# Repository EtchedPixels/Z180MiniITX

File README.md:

# Z180 Mini-ITX Mother Board

This very much an initial work in progress.

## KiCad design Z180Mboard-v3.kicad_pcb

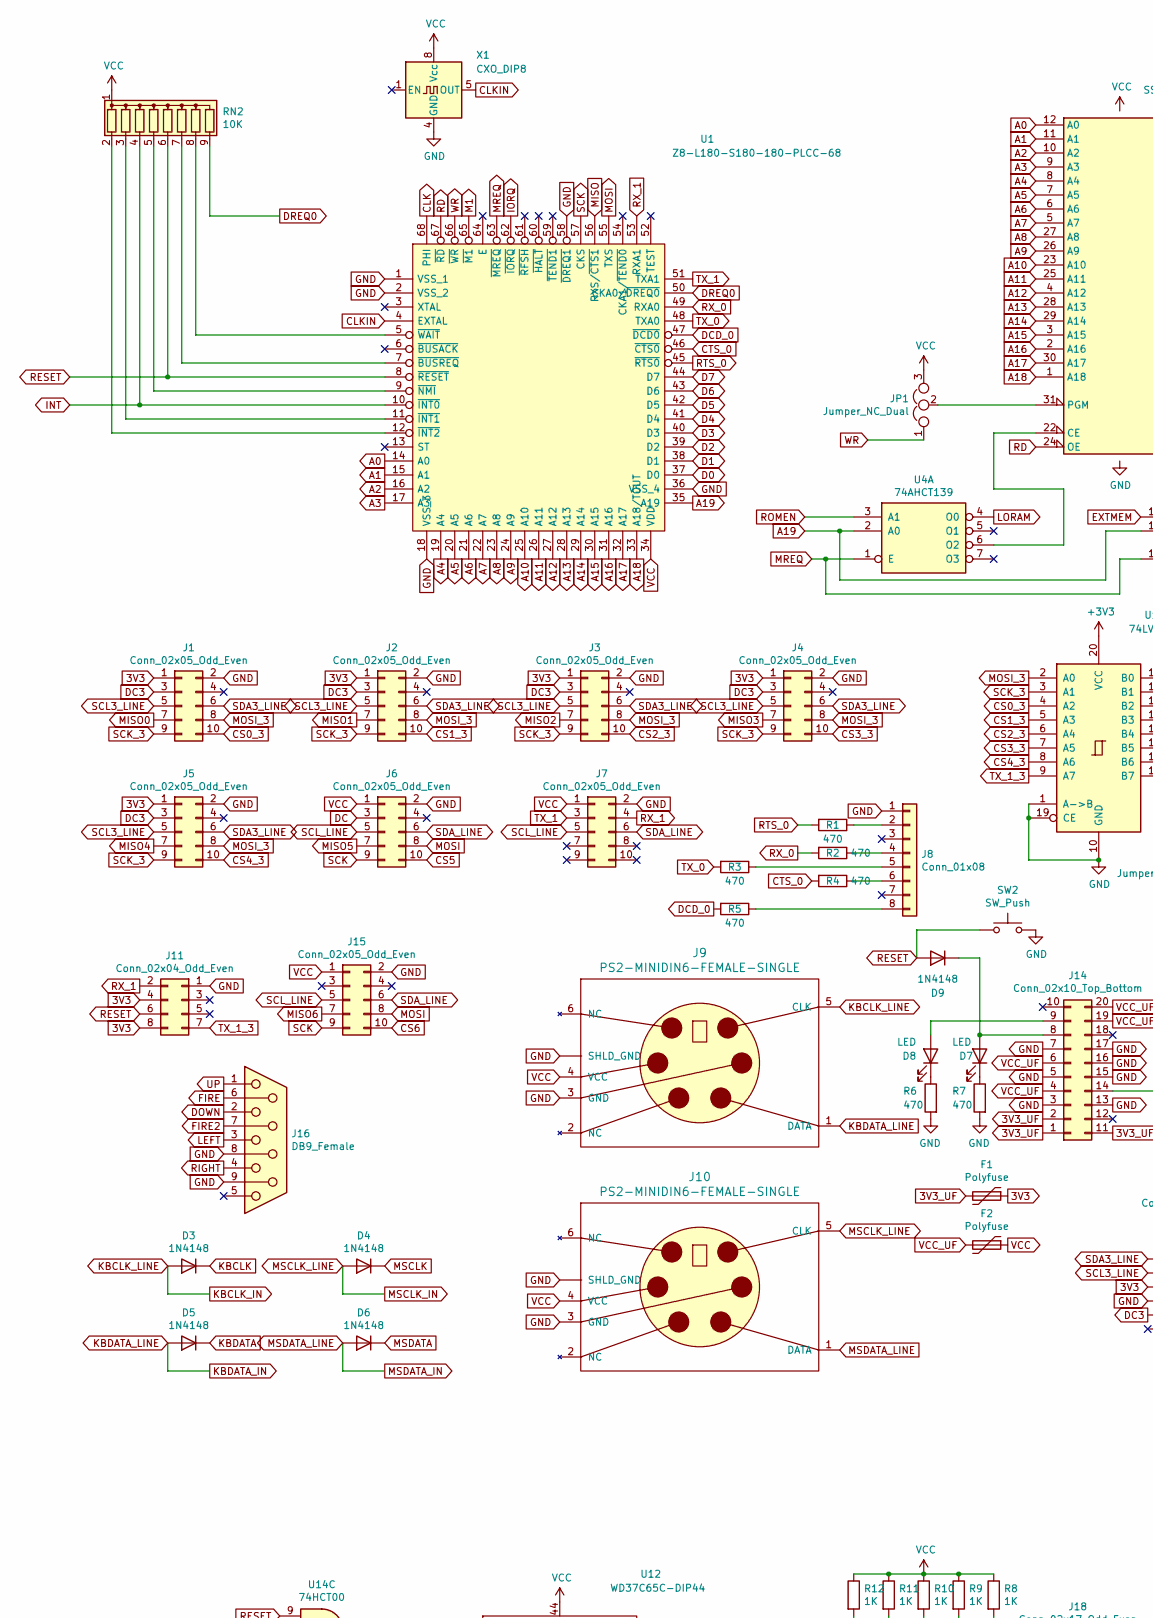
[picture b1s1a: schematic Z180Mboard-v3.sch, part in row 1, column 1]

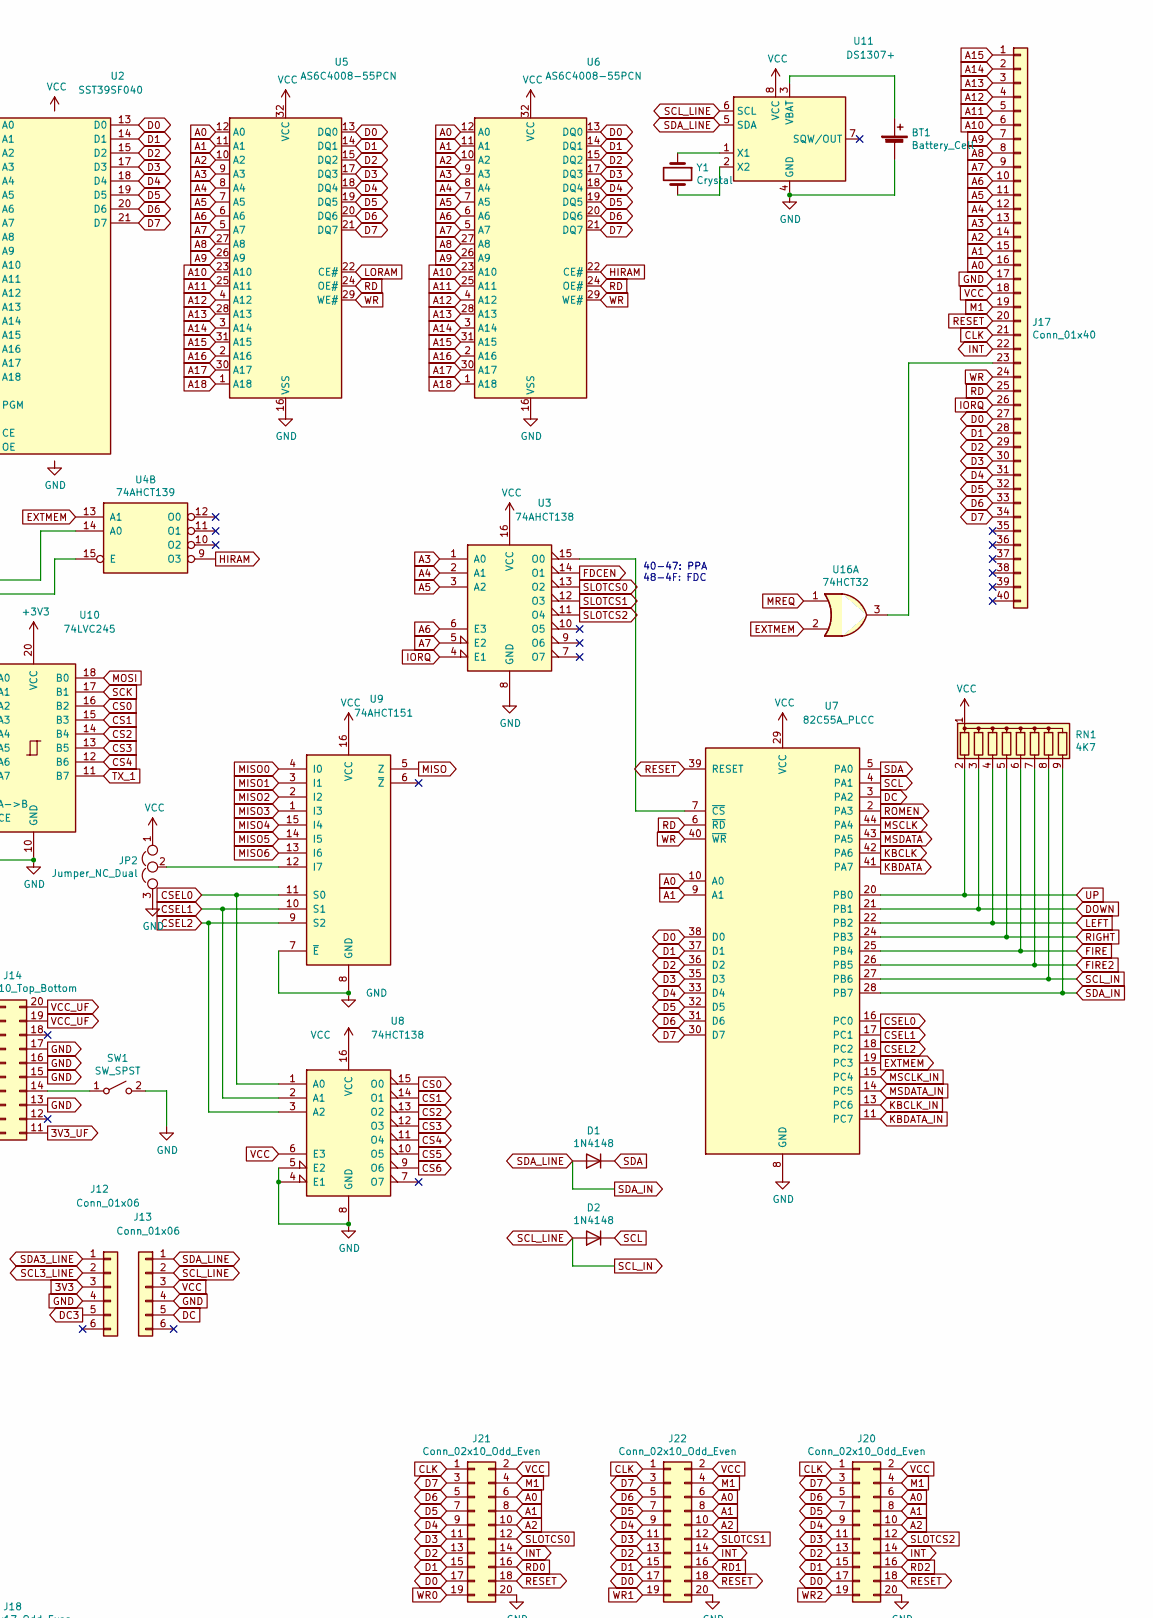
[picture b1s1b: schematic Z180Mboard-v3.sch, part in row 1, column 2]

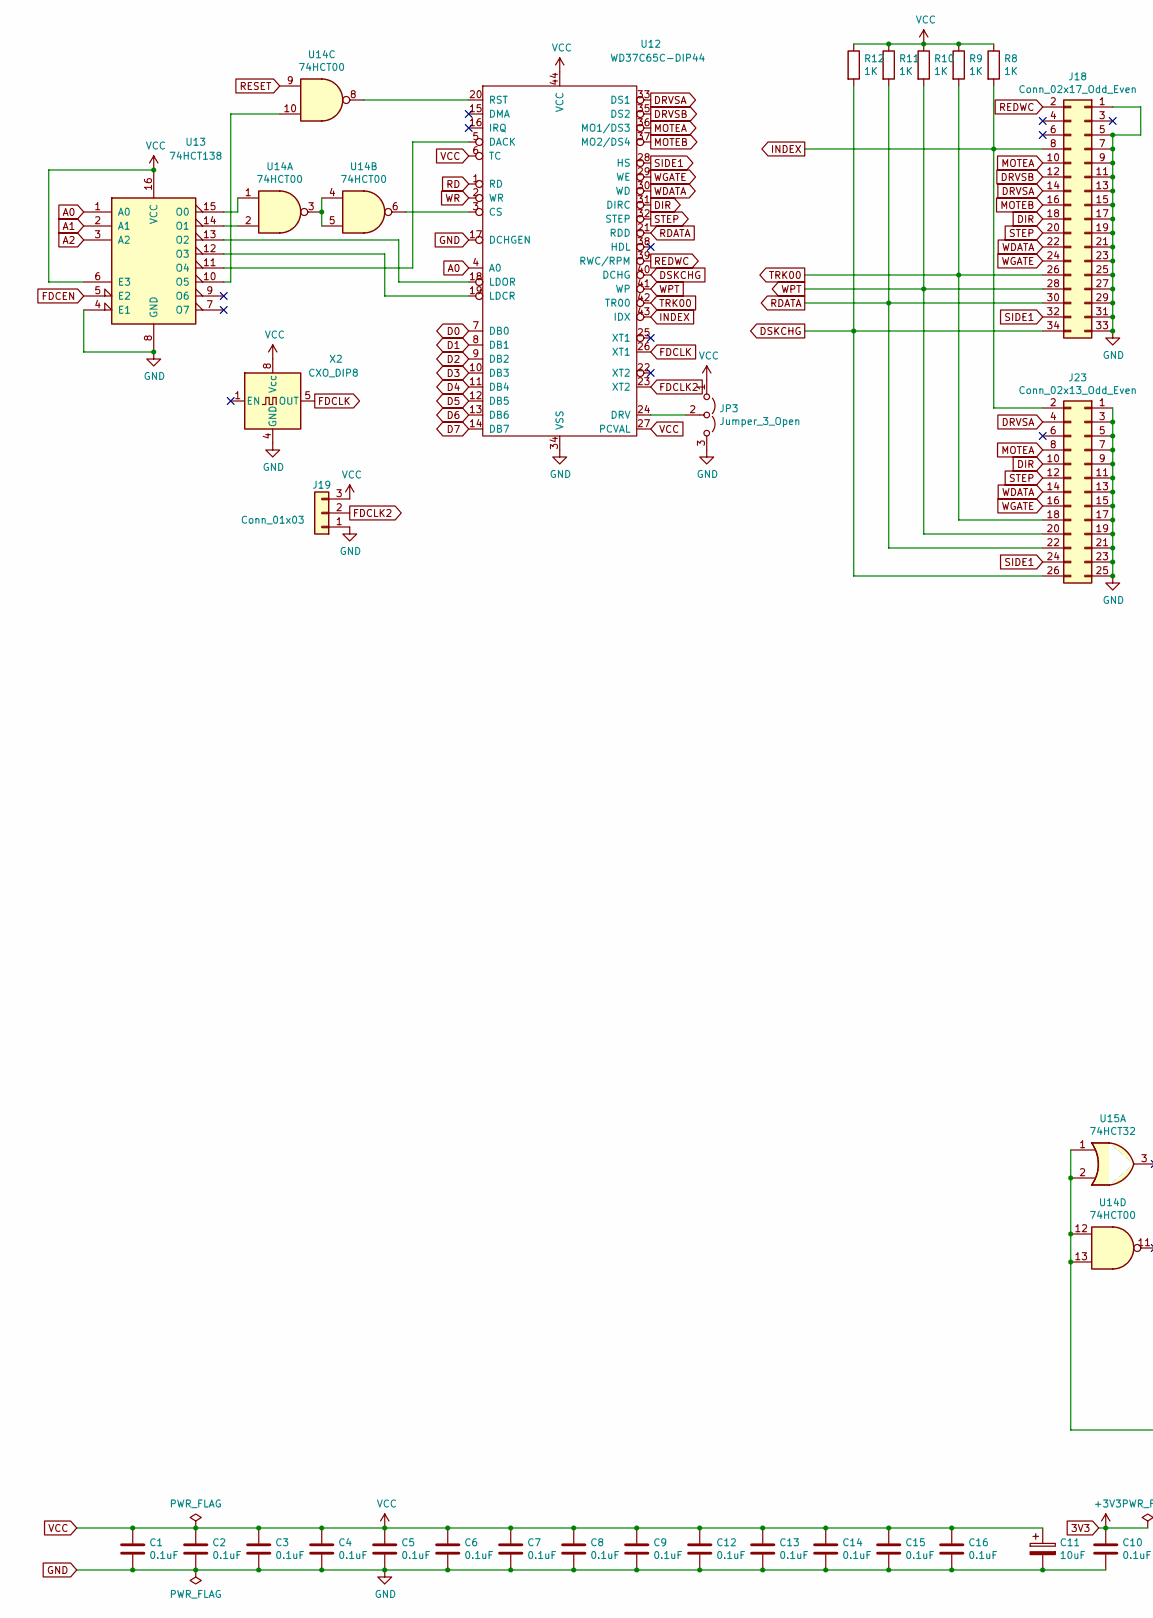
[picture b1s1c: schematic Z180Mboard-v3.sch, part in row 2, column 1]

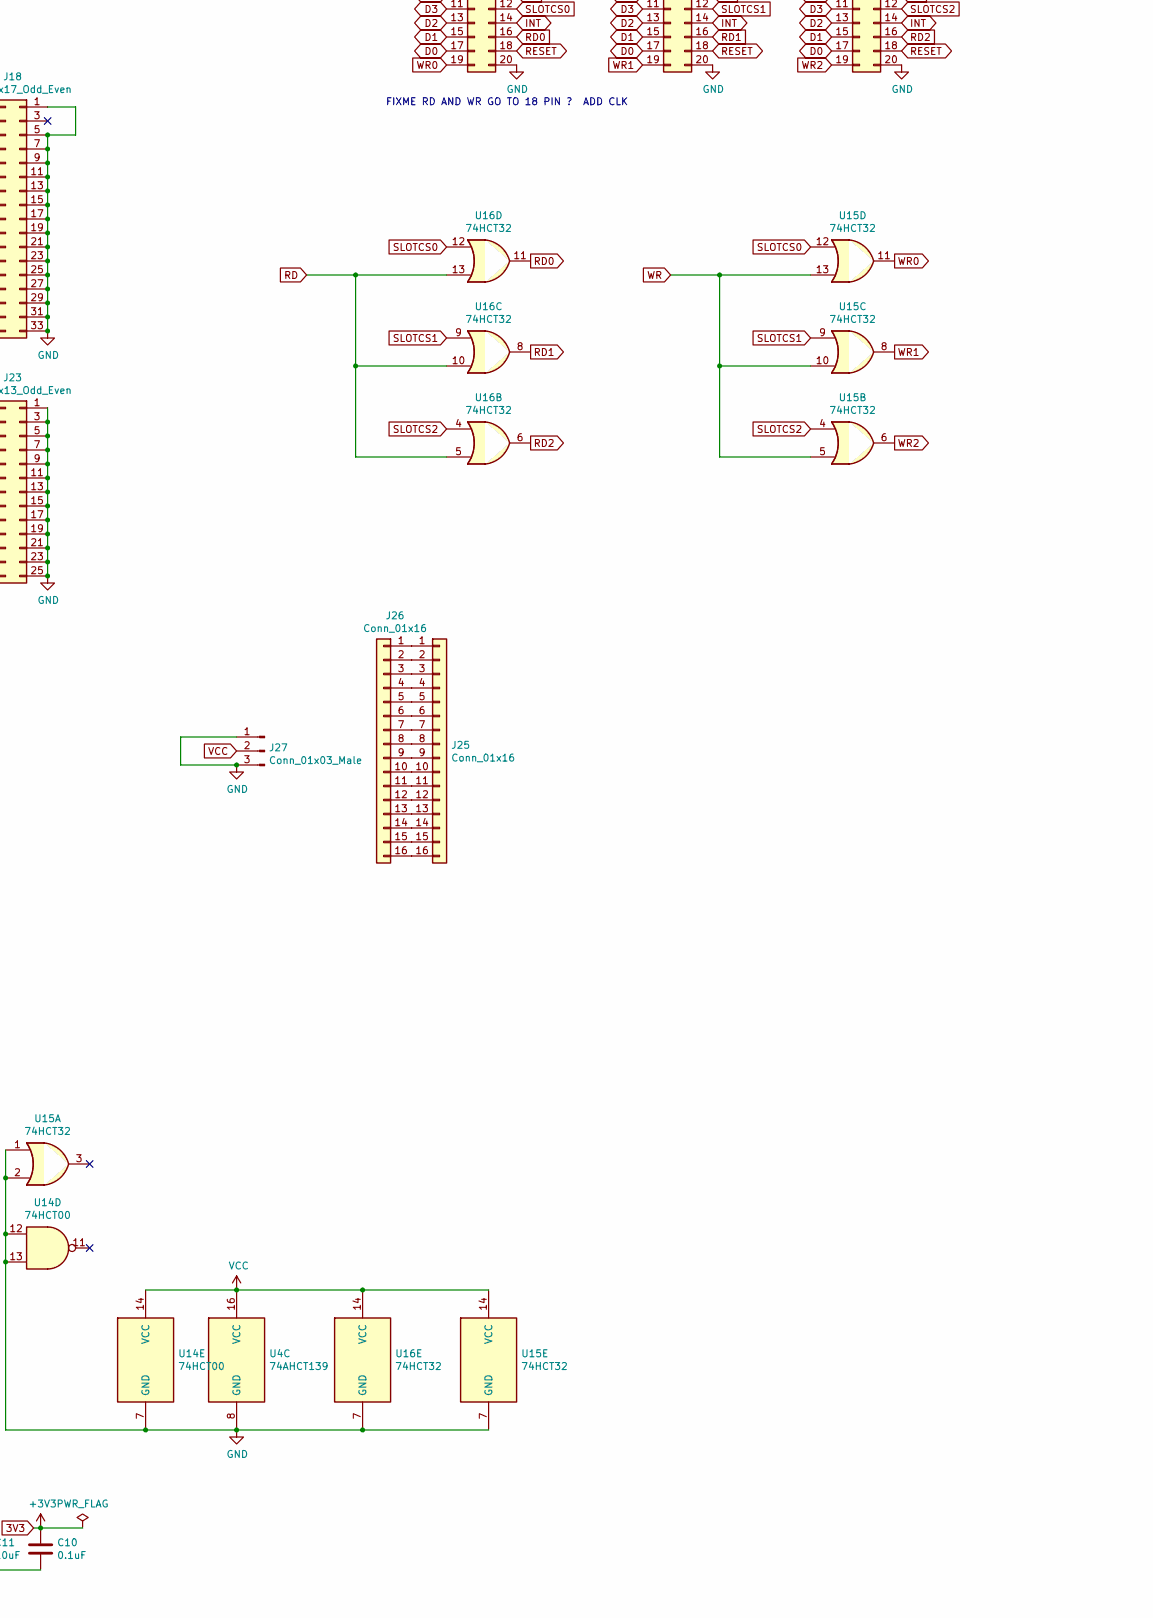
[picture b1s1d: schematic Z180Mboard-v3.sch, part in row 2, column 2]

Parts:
BT1: Battery_Cell; BatteryHolder_Keystone_1060_1x2032
C1, C2, C3, C4, C5, C6, C7, C8, C9, C10, C12, C13, C14, C15, C16: 0.1uF; C_Disc_D3.0mm_W2.0mm_P2.50mm
C11: 10uF; CP_Radial_D10.0mm_P3.50mm
D1, D2, D3, D4, D5, D6, D9: 1N4148; D_DO-35_SOD27_P7.62mm_Horizontal
D7, D8: LED; PinHeader_1x02_P2.54mm_Vertical
F1, F2: Polyfuse; Fuse_Littelfuse-LVR100
J1, J2, J3, J4, J5, J6, J7, J15: Conn_02x05_Odd_Even; IDC-Header_2x05_P2.54mm_Vertical
J8: Conn_01x08; PinSocket_1x08_P2.54mm_Horizontal
J9, J10: PS2-MINIDIN6-FEMALE-SINGLE; MINI-DIN-6-FULL-SHIELD
J11: Conn_02x04_Odd_Even; PinSocket_2x04_P2.54mm_Vertical
J12, J13: Conn_01x06; PinHeader_1x06_P2.54mm_Vertical
J14: Conn_02x10_Top_Bottom; Molex_Mini-Fit_Jr_5566-20A_2x10_P4.20mm_Vertical
J16: DB9_Female; DSUB-9_Female_Horizontal_P2.77x2.54mm_EdgePinOffset9.40mm
J17: Conn_01x40; PinSocket_1x40_P2.54mm_Vertical
J18: Conn_02x17_Odd_Even; IDC-Header_2x17_P2.54mm_Vertical
J19: Conn_01x03; PinHeader_1x03_P2.54mm_Vertical
J20, J21, J22: Conn_02x10_Odd_Even; PinSocket_2x10_P2.54mm_Vertical
J23: Conn_02x13_Odd_Even; IDC-Header_2x13_P2.54mm_Vertical
J25: Conn_01x16; PinHeader_1x16_P2.54mm_Horizontal
J26: Conn_01x16; PinHeader_1x16_P2.54mm_Vertical
J27: Conn_01x03_Male; PinHeader_1x03_P2.54mm_Vertical
JP1, JP2: Jumper_NC_Dual; PinHeader_1x03_P2.54mm_Vertical
JP3: Jumper_3_Open; PinHeader_1x03_P2.54mm_Vertical
R1, R2, R3, R4, R5, R6, R7: 470; R_Axial_DIN0207_L6.3mm_D2.5mm_P7.62mm_Horizontal
R8, R9, R10, R11, R12: 1K; R_Axial_DIN0207_L6.3mm_D2.5mm_P7.62mm_Horizontal
RN1: 4K7; R_Array_SIP9
RN2: 10K; R_Array_SIP9
SW1: SW_SPST; PinHeader_1x02_P2.54mm_Vertical
SW2: SW_Push; PinHeader_1x02_P2.54mm_Vertical
U1: Z8-L180-S180-180-PLCC-68; PLCC-68_THT-Socket; Manufacturer_Part_Number Z8S18033VSG; Mouser Part Number 692-Z8S18033VSG
U2: SST39SF040; DIP-32_W15.24mm_Socket
U3: 74AHCT138; DIP-16_W7.62mm_Socket
U4: 74AHCT139; DIP-16_W7.62mm_Socket
U5, U6: AS6C4008-55PCN; DIP-32_W15.24mm
U7: 82C55A_PLCC; PLCC-44_THT-Socket
U8, U13: 74HCT138; DIP-16_W7.62mm_Socket
U9: 74AHCT151; DIP-16_W7.62mm_Socket
U10: 74LVC245; DIP-20_W7.62mm_Socket
U11: DS1307+; DIP-8_W7.62mm
U12: WD37C65C-DIP44; PLCC-44_THT-Socket
U14: 74HCT00; DIP-14_W7.62mm_Socket
U15, U16: 74HCT32; DIP-14_W7.62mm_Socket
X1, X2: CXO_DIP8; Oscillator_DIP-8
Y1: Crystal; Crystal_C26-LF_D2.1mm_L6.5mm_Vertical

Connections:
3V3: C10.1, F1.1, J1.1, J2.1, J3.1, J4.1, J5.1, J11.4, J11.8, J12.3, U10.20 (VCC)
3V3_UF: F1.2, J14.1, J14.2, J14.11
A0: J17.16, J20.6, J21.6, J22.6, U1.14 (A0), U2.12 (A0), U5.12 (A0), U6.12 (A0), U7.10 (A0), U12.4 (A0), U13.1 (A0)
A1: J17.15, J20.8, J21.8, J22.8, U1.15 (A1), U2.11 (A1), U5.11 (A1), U6.11 (A1), U7.9 (A1), U13.2 (A1)
A2: J17.14, J20.10, J21.10, J22.10, U1.16 (A2), U2.10 (A2), U5.10 (A2), U6.10 (A2), U13.3 (A2)
A3: J17.13, U1.17 (A3), U2.9 (A3), U3.1 (A0), U5.9 (A3), U6.9 (A3)
A4: J17.12, U1.19 (A4), U2.8 (A4), U3.2 (A1), U5.8 (A4), U6.8 (A4)
A5: J17.11, U1.20 (A5), U2.7 (A5), U3.3 (A2), U5.7 (A5), U6.7 (A5)
A6: J17.10, U1.21 (A6), U2.6 (A6), U3.6 (E3), U5.6 (A6), U6.6 (A6)
A7: J17.9, U1.22 (A7), U2.5 (A7), U3.5 (E2), U5.5 (A7), U6.5 (A7)
A8: J17.8, U1.23 (A8), U2.27 (A8), U5.27 (A8), U6.27 (A8)
A9: J17.7, U1.24 (A9), U2.26 (A9), U5.26 (A9), U6.26 (A9)
A10: J17.6, U1.25 (A10), U2.23 (A10), U5.23 (A10), U6.23 (A10)
A11: J17.5, U1.26 (A11), U2.25 (A11), U5.25 (A11), U6.25 (A11)
A12: J17.4, U1.27 (A12), U2.4 (A12), U5.4 (A12), U6.4 (A12)
A13: J17.3, U1.28 (A13), U2.28 (A13), U5.28 (A13), U6.28 (A13)
A14: J17.2, U1.29 (A14), U2.29 (A14), U5.3 (A14), U6.3 (A14)
A15: J17.1, U1.30 (A15), U2.3 (A15), U5.31 (A15), U6.31 (A15)
A16: U1.31 (A16), U2.2 (A16), U5.2 (A16), U6.2 (A16)
A17: U1.32 (A17), U2.30 (A17), U5.30 (A17), U6.30 (A17)
A18: U1.33 (A18/TOUT), U2.1 (A18), U5.1 (A18), U6.1 (A18)
A19: U1.35 (A19), U4.2 (A0), U4.14 (A0)
CLK: J17.21, J20.1, J21.1, J22.1, U1.68 (PHI)
CLKIN: U1.4 (EXTAL), X1.5 (OUT)
CS0: U8.15 (O0), U10.16 (B2)
CS0_3: J1.10, U10.4 (A2)
CS1: U8.14 (O1), U10.15 (B3)
CS1_3: J2.10, U10.5 (A3)
CS2: U8.13 (O2), U10.14 (B4)
CS2_3: J3.10, U10.6 (A4)
CS3: U8.12 (O3), U10.13 (B5)
CS3_3: J4.10, U10.7 (A5)
CS4: U8.11 (O4), U10.12 (B6)
CS4_3: J5.10, U10.8 (A6)
CS5: J6.10, U8.10 (O5)
CS6: J15.10, U8.9 (O6)
CSEL0: U7.16 (PC0), U8.1 (A0), U9.11 (S0)
CSEL1: U7.17 (PC1), U8.2 (A1), U9.10 (S1)
CSEL2: U7.18 (PC2), U8.3 (A2), U9.9 (S2)
CTS_0: R4.2, U1.46 (~CTS0)
D0: J17.27, J20.17, J21.17, J22.17, U1.37 (D0), U2.13 (D0), U5.13 (DQ0), U6.13 (DQ0), U7.38 (D0), U12.7 (DB0)
D1: J17.28, J20.15, J21.15, J22.15, U1.38 (D1), U2.14 (D1), U5.14 (DQ1), U6.14 (DQ1), U7.37 (D1), U12.8 (DB1)
D2: J17.29, J20.13, J21.13, J22.13, U1.39 (D2), U2.15 (D2), U5.15 (DQ2), U6.15 (DQ2), U7.36 (D2), U12.9 (DB2)
D3: J17.30, J20.11, J21.11, J22.11, U1.40 (D3), U2.17 (D3), U5.17 (DQ3), U6.17 (DQ3), U7.35 (D3), U12.10 (DB3)
D4: J17.31, J20.9, J21.9, J22.9, U1.41 (D4), U2.18 (D4), U5.18 (DQ4), U6.18 (DQ4), U7.33 (D4), U12.11 (DB4)
D5: J17.32, J20.7, J21.7, J22.7, U1.42 (D5), U2.19 (D5), U5.19 (DQ5), U6.19 (DQ5), U7.32 (D5), U12.12 (DB5)
D6: J17.33, J20.5, J21.5, J22.5, U1.43 (D6), U2.20 (D6), U5.20 (DQ6), U6.20 (DQ6), U7.31 (D6), U12.13 (DB6)
D7: J17.34, J20.3, J21.3, J22.3, U1.44 (D7), U2.21 (D7), U5.21 (DQ7), U6.21 (DQ7), U7.30 (D7), U12.14 (DB7)
DC: J6.3, J13.5, U7.3 (PA2)
DC3: J1.3, J2.3, J3.3, J4.3, J5.3, J12.5
DCD_0: R5.2, U1.47 (~DCD0)
DIR: J18.18, J23.10, U12.31 (DIRC)
DOWN: J16.2, RN1.3 (R2), U7.21 (PB1)
DREQ0: RN2.9 (R8), U1.50 (CKA0/~DREQ0)
DRVSA: J18.14, J23.4, U12.33 (DS1)
DRVSB: J18.12, U12.35 (DS2)
DSKCHG: J18.34, J23.26, R12.2, U12.40 (DCHG)
EXTMEM: U4.13 (A1), U7.19 (PC3), U16.2
FDCEN: U3.14 (O1), U13.5 (E2)
FDCLK: U12.26 (XT1), X2.5 (OUT)
FDCLK2: J19.2, U12.23 (XT2)
FIRE: J16.6, RN1.6 (R5), U7.25 (PB4)
FIRE2: J16.7, RN1.7 (R6), U7.26 (PB5)
GND: BT1.2 (-), C1.2, C2.2, C3.2, C4.2, C5.2, C6.2, C7.2, C8.2, C9.2, C10.2, C11.2, C12.2, C13.2, C14.2, C15.2, C16.2, J1.2, J2.2, J3.2, J4.2, J5.2, J6.2, J7.2, J8.1, J9.3 (GND), J9.~ (SHLD_GND), J10.3 (GND), J10.~ (SHLD_GND), J11.1, J12.4, J13.4, J14.3, J14.5, J14.7, J14.13, J14.15, J14.16, J14.17, J15.2, J16.8, J16.9, J17.17, J18.1, J18.5, J18.7, J18.9, J18.11, J18.13, J18.15, J18.17, J18.19, J18.21, J18.23, J18.25, J18.27, J18.29, J18.31, J18.33, J19.1, J20.20, J21.20, J22.20, J23.1, J23.3, J23.5, J23.7, J23.9, J23.11, J23.13, J23.15, J23.17, J23.19, J23.21, J23.23, J23.25, J27.1, J27.3, JP2.3, JP3.3 (B), R6.2, R7.2, SW1.2 (B), SW2.2, U1.1 (VSS_1), U1.2 (VSS_2), U1.18 (VSS_3), U1.36 (VSS_4), U1.58 (~DREQ1), U2.16 (GND), U3.8 (GND), U4.8 (GND), U5.16 (VSS), U6.16 (VSS), U7.8 (GND), U8.4 (E1), U8.5 (E2), U8.8 (GND), U9.7 (~E), U9.8 (GND), U10.1 (A->B), U10.10 (GND), U10.19 (CE), U11.4 (GND), U12.17 (DCHGEN), U12.34 (VSS), U13.4 (E1), U13.8 (GND), U14.7 (GND), U14.12, U14.13, U15.1, U15.2, U15.7 (GND), U16.7 (GND), X1.4 (GND), X2.4 (GND)
HIRAM: U4.9 (O3), U6.22 (CE#)
INDEX: J18.8, J23.2, R8.2, U12.43 (IDX)
INT: J17.22, J20.14, J21.14, J22.14, RN2.4 (R3), U1.10 (~INT0)
IORQ: J17.26, U1.62 (~IORQ), U3.4 (E1)
KBCLK: D3.1 (K), U7.42 (PA6)
KBCLK_IN: D3.2 (A), J9.5 (CLK), U7.13 (PC6)
KBDATA: D5.1 (K), U7.41 (PA7)
KBDATA_IN: D5.2 (A), J9.1 (DATA), U7.11 (PC7)
LEFT: J16.3, RN1.4 (R3), U7.22 (PB2)
LORAM: U4.4 (O0), U5.22 (CE#)
M1: J17.19, J20.4, J21.4, J22.4, U1.65 (~M1)
MISO: U1.56 (RXS/~CTS1), U9.5 (Z)
MISO0: J1.7, U9.4 (I0)
MISO1: J2.7, U9.3 (I1)
MISO2: J3.7, U9.2 (I2)
MISO3: J4.7, U9.1 (I3)
MISO4: J5.7, U9.15 (I4)
MISO5: J6.7, U9.14 (I5)
MISO6: J15.7, U9.13 (I6)
MOSI: J6.8, J15.8, U1.55 (TXS), U10.18 (B0)
MOSI_3: J1.8, J2.8, J3.8, J4.8, J5.8, U10.2 (A0)
MOTEA: J18.10, J23.8, U12.36 (MO1/DS3)
MOTEB: J18.16, U12.37 (MO2/DS4)
MREQ: U1.63 (~MREQ), U4.1 (E), U4.15 (E), U16.1
MSCLK: D4.1 (K), U7.44 (PA4)
MSCLK_IN: D4.2 (A), J10.5 (CLK), U7.15 (PC4)
MSDATA: D6.1 (K), U7.43 (PA5)
MSDATA_IN: D6.2 (A), J10.1 (DATA), U7.14 (PC5)
unnamed: BT1.1 (+), U11.3 (VBAT)
unnamed: D7.1 (K), R7.1
unnamed: D7.2 (A), D9.1 (K), J14.8
unnamed: D8.1 (K), R6.1
unnamed: D8.2 (A), J14.9
unnamed: J8.2, R1.1
unnamed: J8.4, R2.1
unnamed: J8.5, R3.1
unnamed: J8.6, R4.1
unnamed: J8.8, R5.1
unnamed: J14.14, SW1.1 (A)
unnamed: J17.23, U16.3
unnamed: J25.1, J26.1
unnamed: J25.2, J26.2
unnamed: J25.3, J26.3
unnamed: J25.4, J26.4
unnamed: J25.5, J26.5
unnamed: J25.6, J26.6
unnamed: J25.7, J26.7
unnamed: J25.8, J26.8
unnamed: J25.9, J26.9
unnamed: J25.10, J26.10
unnamed: J25.11, J26.11
unnamed: J25.12, J26.12
unnamed: J25.13, J26.13
unnamed: J25.14, J26.14
unnamed: J25.15, J26.15
unnamed: J25.16, J26.16
unnamed: JP1.2, U2.31 (PGM)
unnamed: JP2.2, U9.12 (I7)
unnamed: JP3.2 (C), U12.24 (DRV)
unnamed: RN2.2 (R1), U1.12 (~INT2)
unnamed: RN2.3 (R2), U1.11 (~INT1)
unnamed: RN2.5 (R4), U1.9 (~NMI)
unnamed: RN2.7 (R6), U1.7 (~BUSREQ)
unnamed: RN2.8 (R7), U1.5 (~WAIT)
unnamed: U2.22 (CE), U4.6 (O2)
unnamed: U3.15 (O0), U7.7 (~CS~)
unnamed: U11.1 (X1), Y1.1
unnamed: U11.2 (X2), Y1.2
unnamed: U12.3 (CS), U14.6
unnamed: U12.5 (DACK), U13.11 (O4)
unnamed: U12.18 (LDOR), U13.13 (O2)
unnamed: U12.19 (LDCR), U13.12 (O3)
unnamed: U12.20 (RST), U14.8
unnamed: U13.10 (O5), U14.10
unnamed: U13.14 (O1), U14.2
unnamed: U13.15 (O0), U14.1
unnamed: U14.3, U14.4, U14.5
RD: J17.25, U1.67 (~RD), U2.24 (OE), U5.24 (OE#), U6.24 (OE#), U7.6 (~RD~), U12.1 (RD), U16.5, U16.10, U16.13
RD0: J21.16, U16.11
RD1: J22.16, U16.8
RD2: J20.16, U16.6
RDATA: J18.30, J23.22, R11.2, U12.21 (RDD)
REDWC: J18.2, U12.39 (RWC/RPM)
RESET: D9.2 (A), J11.6, J17.20, J20.18, J21.18, J22.18, RN2.6 (R5), SW2.1, U1.8 (~RESET), U7.39 (RESET), U14.9
RIGHT: J16.4, RN1.5 (R4), U7.24 (PB3)
ROMEN: U4.3 (A1), U7.2 (PA3)
RTS_0: R1.2, U1.45 (~RTS0)
RX_0: R2.2, U1.49 (RXA0)
RX_1: J7.4, J11.2, U1.53 (RXA1)
SCK: J6.9, J15.9, U1.57 (CKS), U10.17 (B1)
SCK_3: J1.9, J2.9, J3.9, J4.9, J5.9, U10.3 (A1)
SCL: D2.1 (K), U7.4 (PA1)
SCL3_LINE: J1.5, J2.5, J3.5, J4.5, J5.5, J12.2
SCL_IN: D2.2 (A), J6.5, J7.5, J13.2, J15.5, RN1.8 (R7), U7.27 (PB6), U11.6 (SCL)
SDA: D1.1 (K), U7.5 (PA0)
SDA3_LINE: J1.6, J2.6, J3.6, J4.6, J5.6, J12.1
SDA_IN: D1.2 (A), J6.6, J7.6, J13.1, J15.6, RN1.9 (R8), U7.28 (PB7), U11.5 (SDA)
SIDE1: J18.32, J23.24, U12.28 (HS)
SLOTCS0: J21.12, U3.13 (O2), U15.12, U16.12
SLOTCS1: J22.12, U3.12 (O3), U15.9, U16.9
SLOTCS2: J20.12, U3.11 (O4), U15.4, U16.4
STEP: J18.20, J23.12, U12.32 (STEP)
TRK00: J18.26, J23.18, R9.2, U12.42 (TR00)
TX_0: R3.2, U1.48 (TXA0)
TX_1: J7.3, U1.51 (TXA1), U10.11 (B7)
TX_1_3: J11.7, U10.9 (A7)
UP: J16.1, RN1.2 (R1), U7.20 (PB0)
VCC: C1.1, C2.1, C3.1, C4.1, C5.1, C6.1, C7.1, C8.1, C9.1, C11.1, C12.1, C13.1, C14.1, C15.1, C16.1, F2.1, J6.1, J7.1, J9.4 (VCC), J10.4 (VCC), J13.3, J15.1, J17.18, J19.3, J20.2, J21.2, J22.2, J27.2, JP1.3, JP2.1, JP3.1 (A), R8.1, R9.1, R10.1, R11.1, R12.1, RN1.1 (common), RN2.1 (common), U1.34 (VDD), U2.32 (VCC), U3.16 (VCC), U4.16 (VCC), U5.32 (VCC), U6.32 (VCC), U7.29 (VCC), U8.6 (E3), U8.16 (VCC), U9.16 (VCC), U11.8 (VCC), U12.6 (TC), U12.27 (PCVAL), U12.44 (VCC), U13.6 (E3), U13.16 (VCC), U14.14 (VCC), U15.14 (VCC), U16.14 (VCC), X1.8 (Vcc), X2.8 (Vcc)
VCC_UF: F2.2, J14.4, J14.6, J14.19, J14.20
WDATA: J18.22, J23.14, U12.30 (WD)
WGATE: J18.24, J23.16, U12.29 (WE)
WPT: J18.28, J23.20, R10.2, U12.41 (WP)
WR: J17.24, JP1.1, U1.66 (~WR), U5.29 (WE#), U6.29 (WE#), U7.40 (~WR~), U12.2 (WR), U15.5, U15.10, U15.13
WR0: J21.19, U15.11
WR1: J22.19, U15.8
WR2: J20.19, U15.6

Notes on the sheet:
40-47: PPA 48-4F: FDC
FIXME RD AND WR GO TO 18 PIN ? ADD CLK

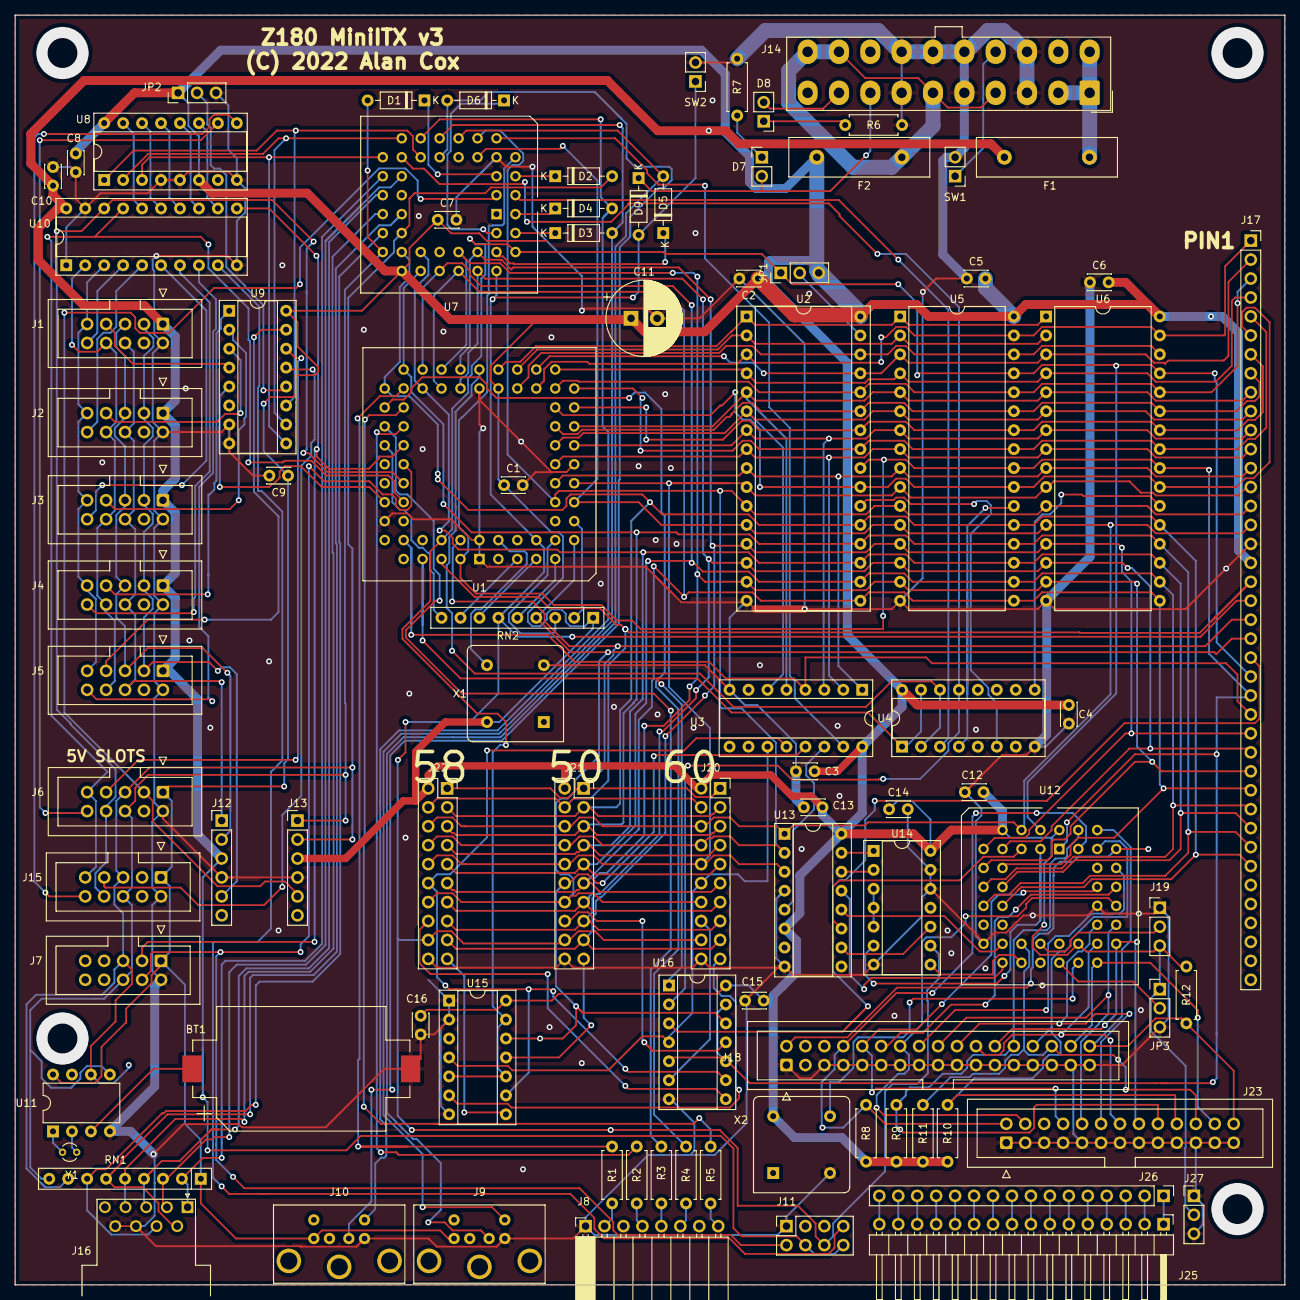
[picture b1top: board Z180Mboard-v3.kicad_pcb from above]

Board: 2 copper layers, 170.2 x 170.2 mm, 92 parts (0 on the bottom side), 180 nets.

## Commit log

2021-08-12 z180mboard: Add the floppy disk interface
2021-08-12 z180mboard: pack things in more tightly, turn the battery vertical
2021-08-13 z180mboard; Add video, holes tidy stuff up
2021-08-14 Z180Mboard: more cleaning up and connector add
2022-03-03 Notes for bugs/mods for v2/v3
2022-03-03 v3: revised board
    - Remove the experimental teletext video
    - Add 3 mini-bus slots instead
    - Relocate FDC to match external card addresses
    - Swap DC and EXTMEM over to fix 82C55 reset glitch problems
    - Remove 5v DC pin from the 3v3 slot
    - Change battery holder
2022-03-06 v3: Hopefully the final revision for this attempt

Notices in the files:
Z180Mboard-v3.kicad_pcb:
(C) 2022 Alan Cox
